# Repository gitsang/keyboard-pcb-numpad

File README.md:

# keyboard-pcb-numpad

## Preview

### SCH

### PCB

### 3D

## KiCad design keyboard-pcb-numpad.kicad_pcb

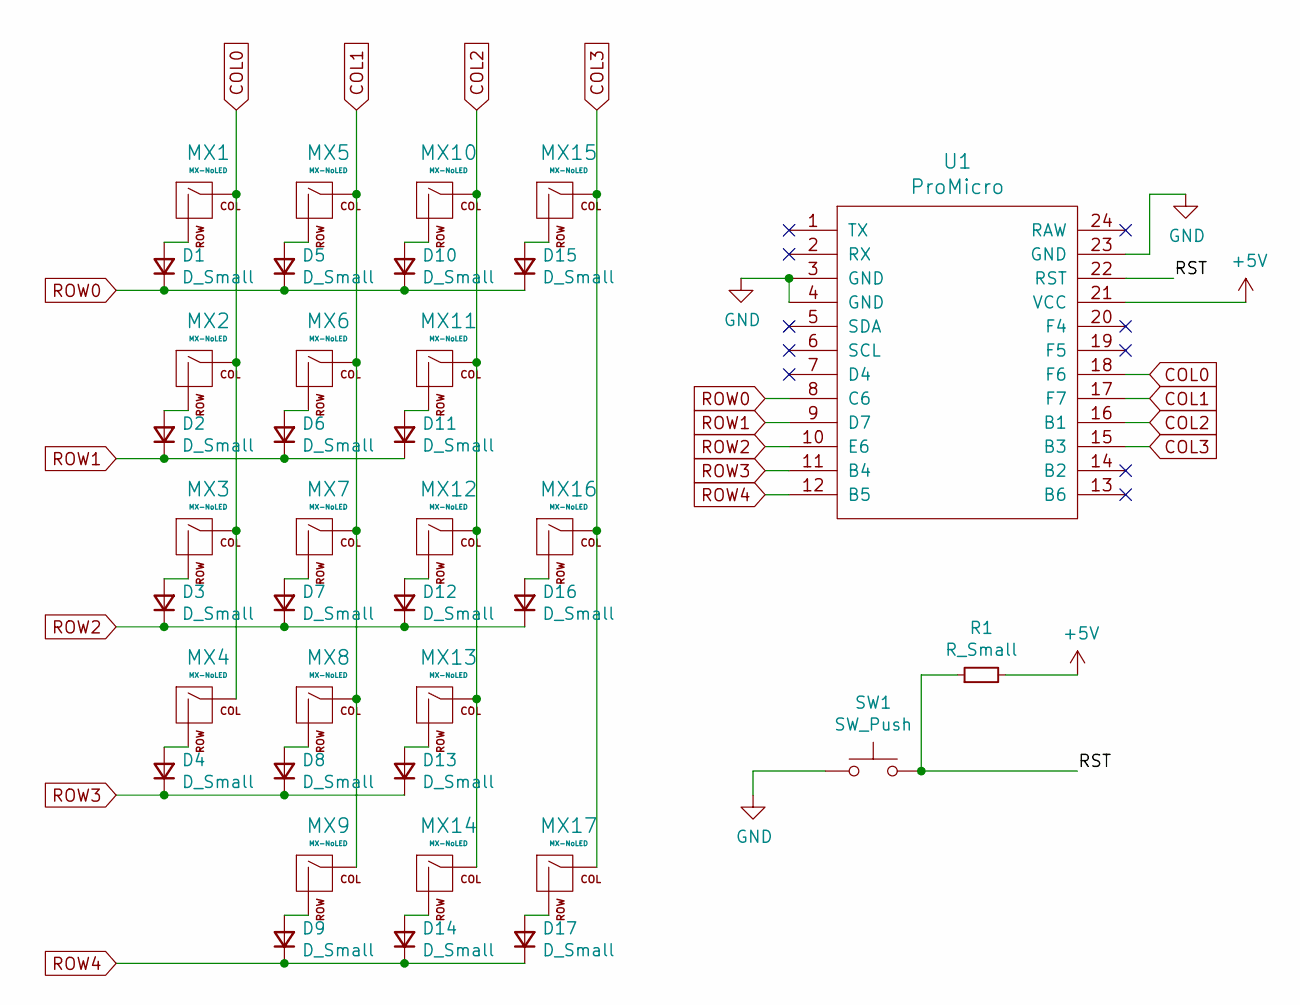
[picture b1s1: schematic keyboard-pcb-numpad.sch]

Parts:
D1, D2, D3, D4, D5, D6, D7, D8, D9, D10, D11, D12, D13, D14, D15, D16, D17: D_Small; D_SOD-123
MX1, MX2, MX3, MX4, MX5, MX6, MX7, MX8, MX9, MX10, MX11, MX12, MX13, MX14, MX15, MX16, MX17: MX-NoLED; MX-1U
R1: R_Small; R_1206_3216Metric
SW1: SW_Push; SKQG-1155865
U1: ProMicro

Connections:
+5V: R1.2, U1.21 (VCC)
/RST: R1.1, SW1.2, U1.22 (RST)
COL0: MX1.1 (COL), MX2.1 (COL), MX3.1 (COL), MX4.1 (COL), U1.18 (F6)
COL1: MX5.1 (COL), MX6.1 (COL), MX7.1 (COL), MX8.1 (COL), MX9.1 (COL), U1.17 (F7)
COL2: MX10.1 (COL), MX11.1 (COL), MX12.1 (COL), MX13.1 (COL), MX14.1 (COL), U1.16 (B1)
COL3: MX15.1 (COL), MX16.1 (COL), MX17.1 (COL), U1.15 (B3)
GND: SW1.1, U1.3 (GND), U1.4 (GND), U1.23 (GND)
unnamed: D1.2 (A), MX1.2 (ROW)
unnamed: D2.2 (A), MX2.2 (ROW)
unnamed: D3.2 (A), MX3.2 (ROW)
unnamed: D4.2 (A), MX4.2 (ROW)
unnamed: D5.2 (A), MX5.2 (ROW)
unnamed: D6.2 (A), MX6.2 (ROW)
unnamed: D7.2 (A), MX7.2 (ROW)
unnamed: D8.2 (A), MX8.2 (ROW)
unnamed: D9.2 (A), MX9.2 (ROW)
unnamed: D10.2 (A), MX10.2 (ROW)
unnamed: D11.2 (A), MX11.2 (ROW)
unnamed: D12.2 (A), MX12.2 (ROW)
unnamed: D13.2 (A), MX13.2 (ROW)
unnamed: D14.2 (A), MX14.2 (ROW)
unnamed: D15.2 (A), MX15.2 (ROW)
unnamed: D16.2 (A), MX16.2 (ROW)
unnamed: D17.2 (A), MX17.2 (ROW)
ROW0: D1.1 (K), D5.1 (K), D10.1 (K), D15.1 (K), U1.8 (C6)
ROW1: D2.1 (K), D6.1 (K), D11.1 (K), U1.9 (D7)
ROW2: D3.1 (K), D7.1 (K), D12.1 (K), D16.1 (K), U1.10 (E6)
ROW3: D4.1 (K), D8.1 (K), D13.1 (K), U1.11 (B4)
ROW4: D9.1 (K), D14.1 (K), D17.1 (K), U1.12 (B5)

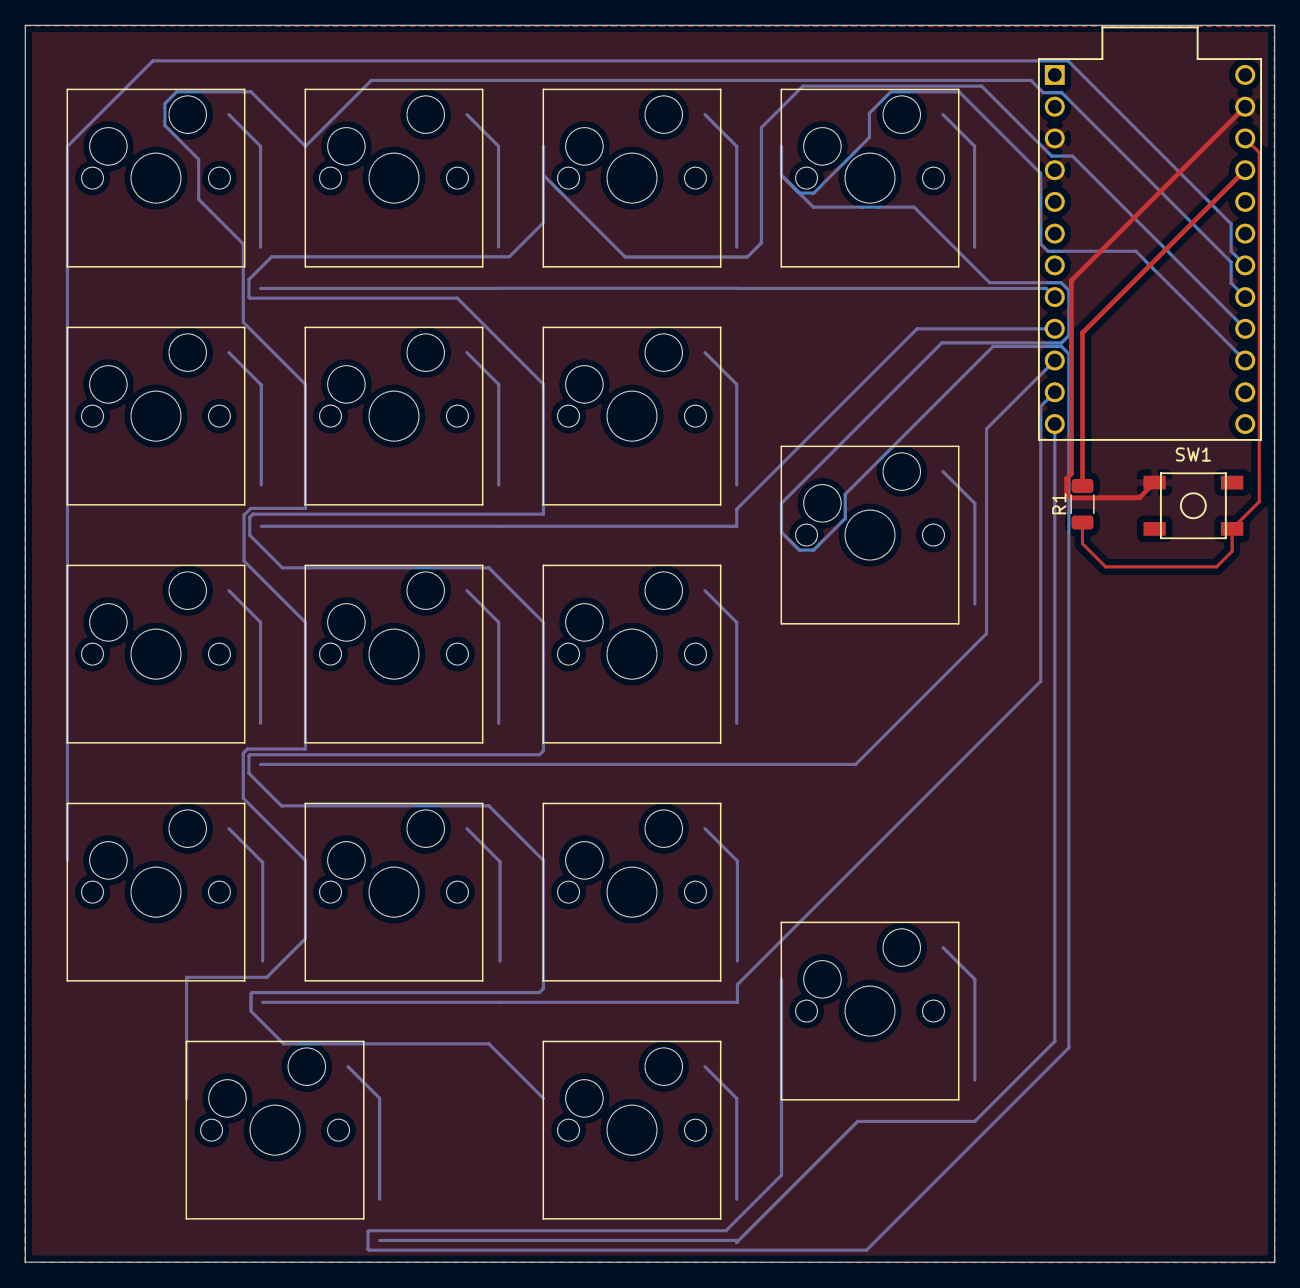
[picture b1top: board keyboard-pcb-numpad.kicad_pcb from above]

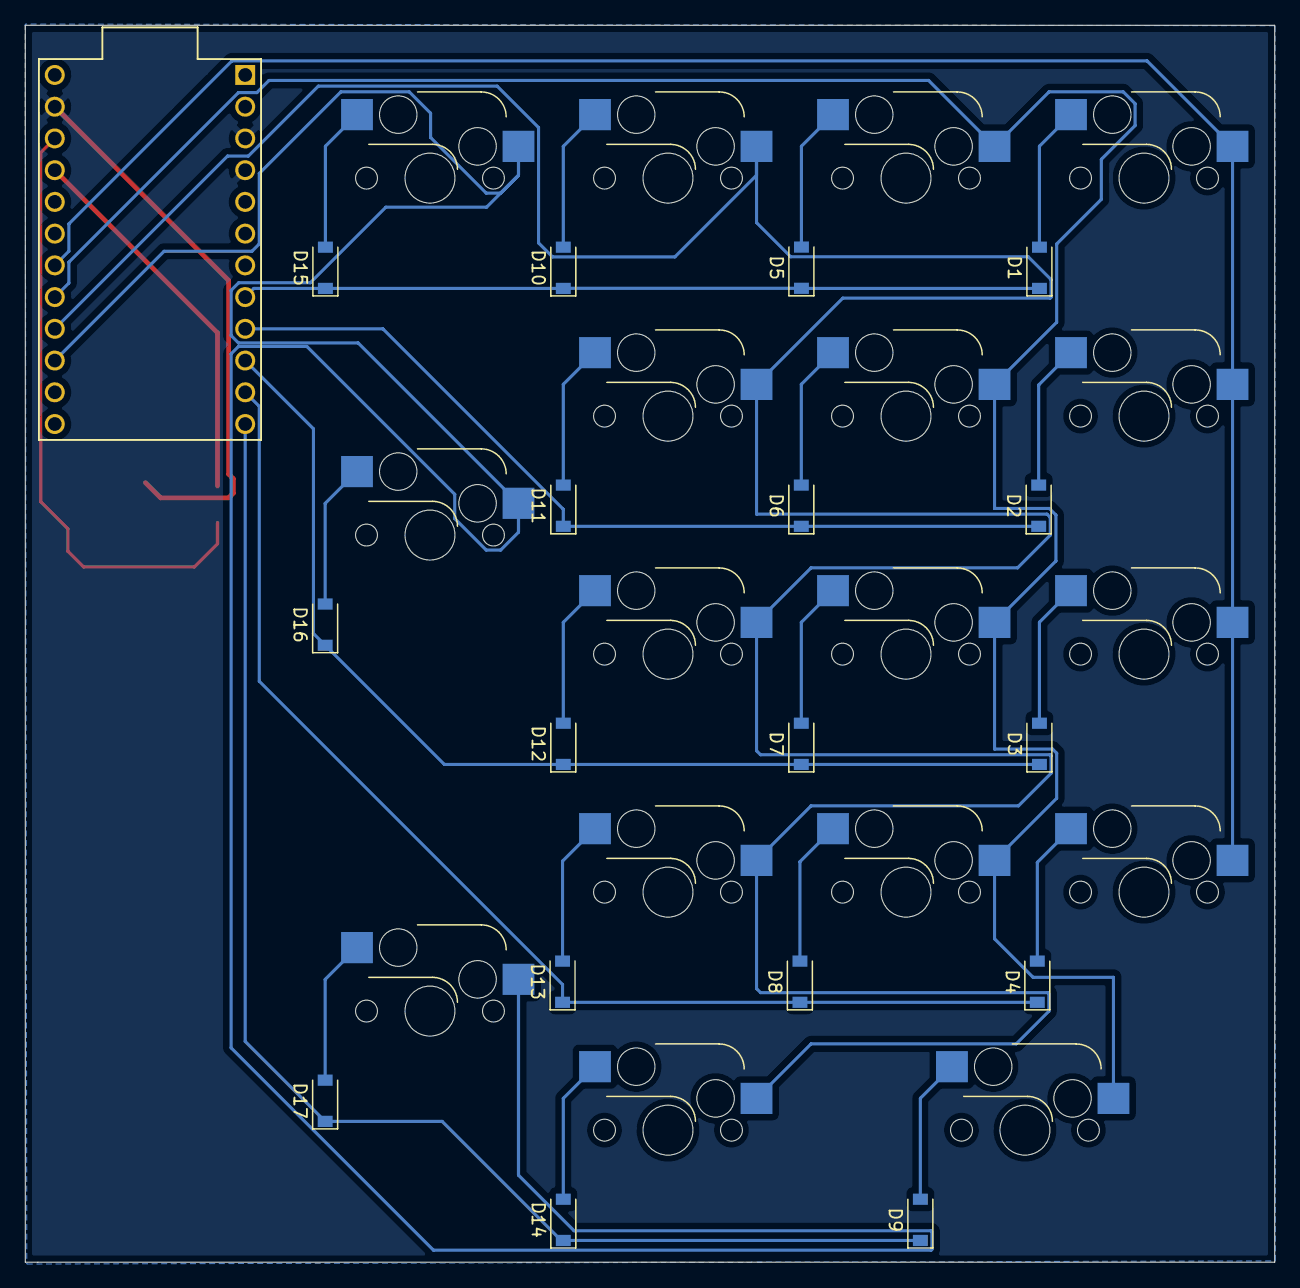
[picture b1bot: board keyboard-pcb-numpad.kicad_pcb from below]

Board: 2 copper layers, 100.0 x 99.0 mm, 37 parts (17 on the bottom side), 29 nets.

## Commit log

2021-10-14 init: init kicad pcb
2021-10-14 init: add submodule
2021-10-14 init: add MIT License
2021-10-14 init: add fp and sym lib
2021-10-14 feat: create mcu schematic
2021-10-14 init: add promicro lib
2021-10-15 feat: complete electrical setup
2021-10-15 feat: assign footprints
2021-10-28 feat: update pcb
2021-10-29 feat: complete route
2021-10-29 fix: fix route
2021-10-29 feat: fill ground
2021-11-02 feat: complete
2021-11-02 chore: add gitignore
2021-11-18 fix: change switch footprints
2021-11-18 docs: update readme
2021-11-18 fix: fix pcb
